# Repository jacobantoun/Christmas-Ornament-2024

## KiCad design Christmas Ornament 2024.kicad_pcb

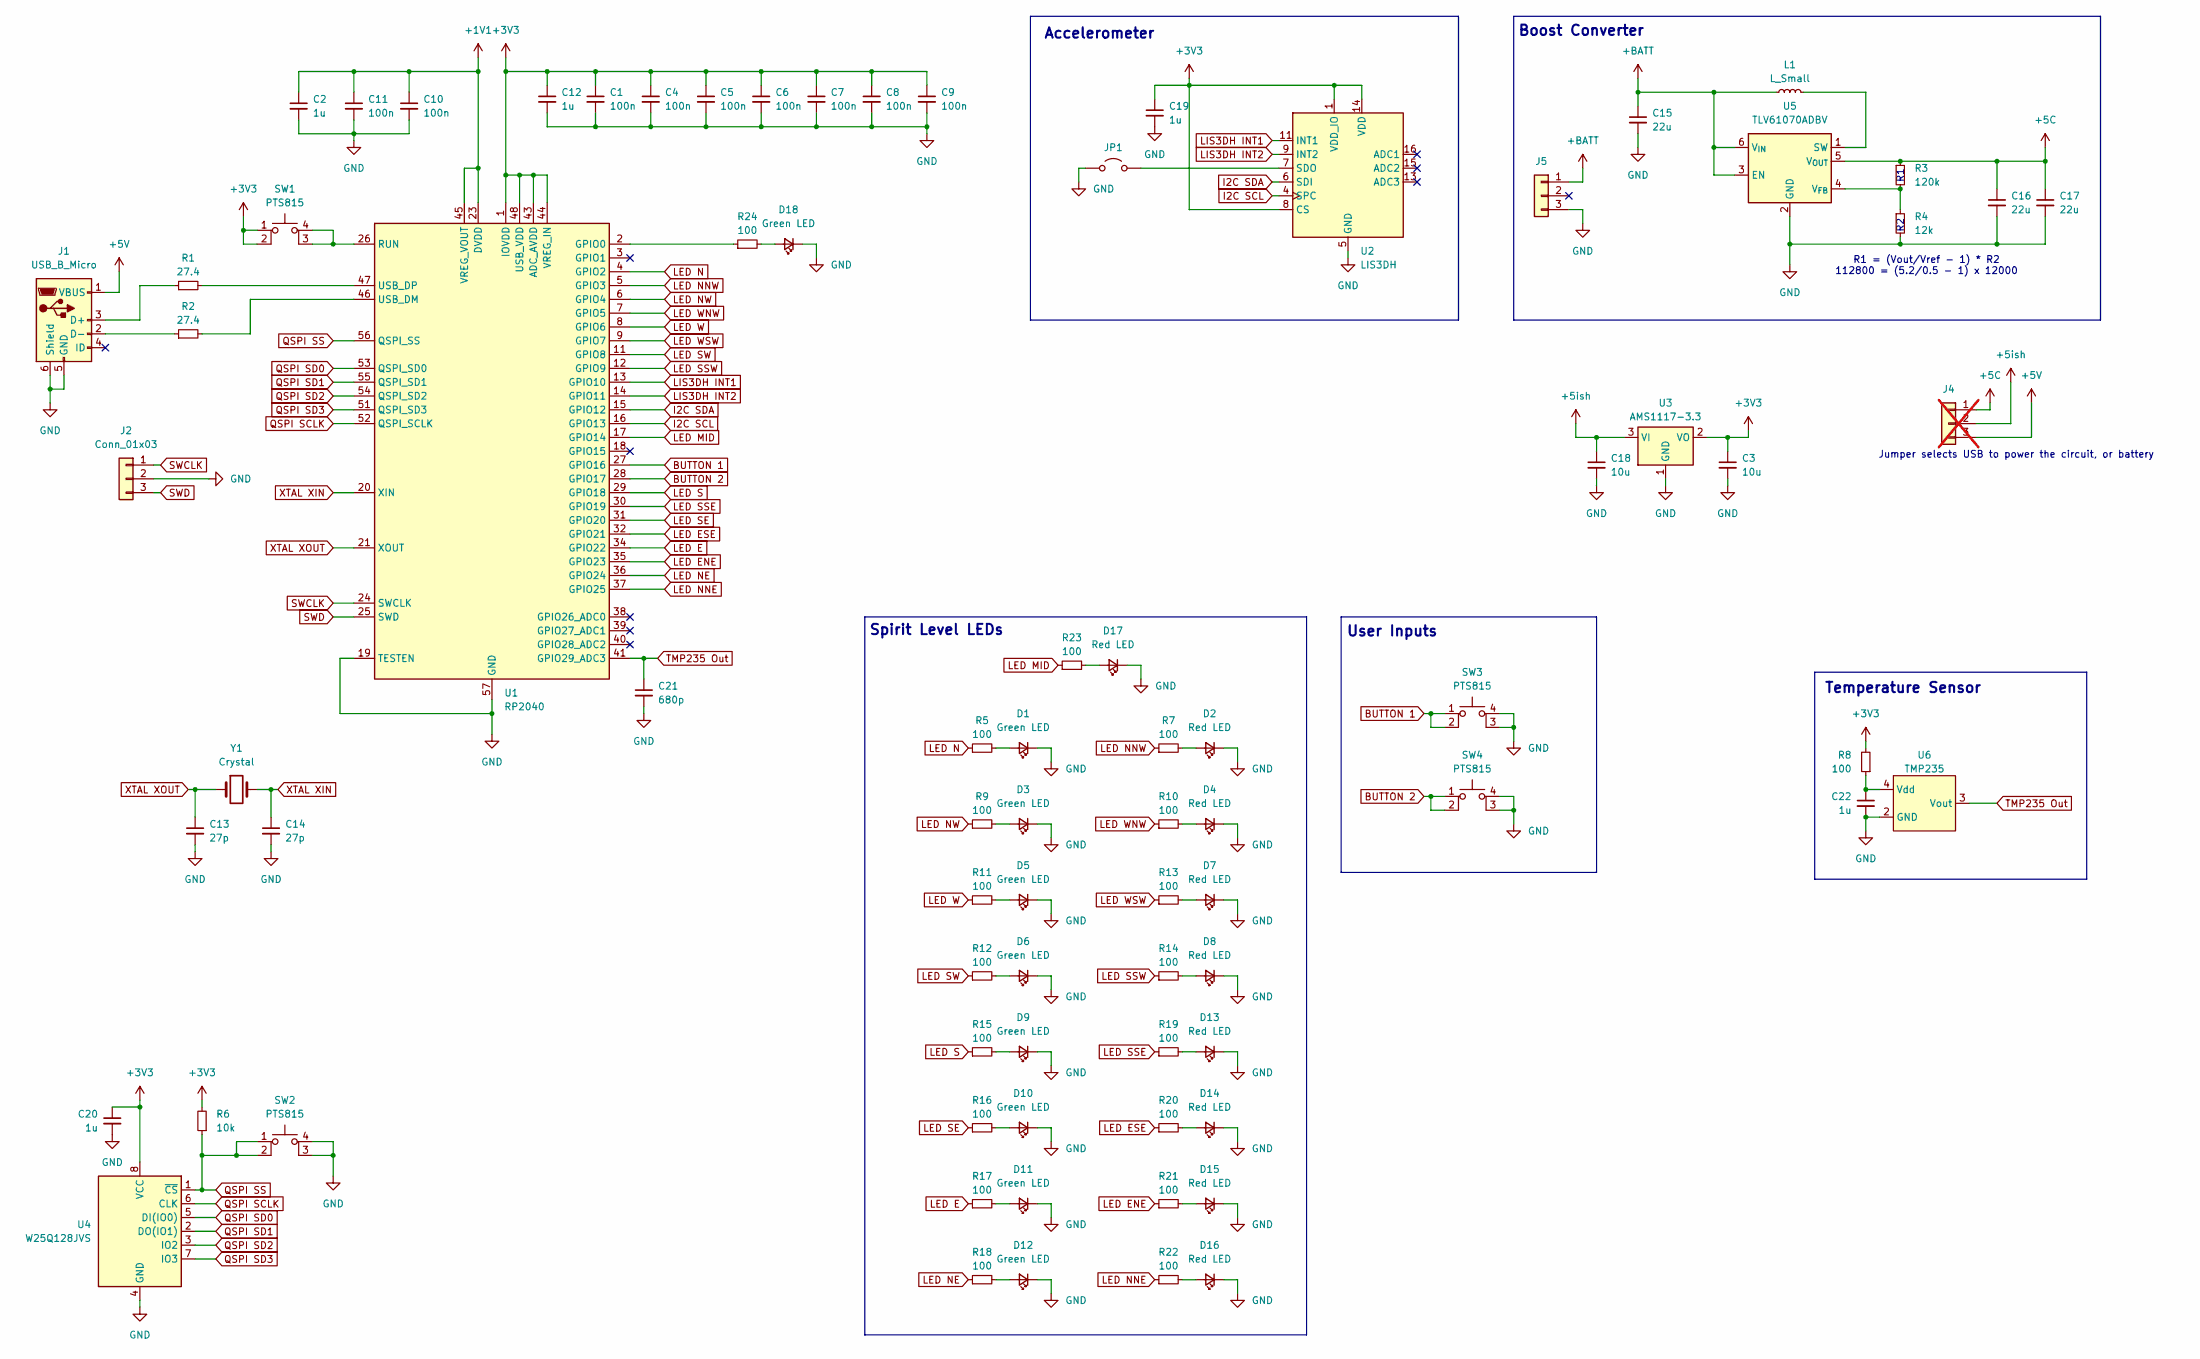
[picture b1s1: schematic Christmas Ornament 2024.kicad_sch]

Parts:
C1, C4, C5, C6, C7, C8, C9, C10, C11: 100n; C_0402_1005Metric_Pad0.74x0.62mm_HandSolder; JLCPCB PN C1525
C2, C12, C19, C20, C22: 1u; C_0402_1005Metric_Pad0.74x0.62mm_HandSolder; JLCPCB PN C52923
C3, C18: 10u; C_0805_2012Metric_Pad1.18x1.45mm_HandSolder; JLCPCB PN C15850
C13, C14: 27p; C_0402_1005Metric_Pad0.74x0.62mm_HandSolder; JLCPCB PN C1557
C15, C16, C17: 22u; C_0805_2012Metric_Pad1.18x1.45mm_HandSolder; JLCPCB PN C45783
C21: 680p; C_0603_1608Metric; JLCPCB PN C1630
D1, D3, D5, D6, D9, D10, D11, D12: Green LED; LED_0805_2012Metric_Pad1.15x1.40mm_HandSolder; JLCPCB PN C2297
D2, D4, D7, D8, D13, D14, D15, D16, D17: Red LED; LED_0805_2012Metric_Pad1.15x1.40mm_HandSolder; JLCPCB PN C2296
D18: Green LED; LED_0805_2012Metric_Pad1.15x1.40mm_HandSolder; JLCPCB PN C2296
J1: USB_B_Micro; USB_Micro-B_Amphenol_10103594-0001LF_Horizontal; JLCPCB PN C428495
J2: Conn_01x03; JST_SH_BM03B-SRSS-TB_1x03-1MP_P1.00mm_Vertical; JLCPCB PN C160389
J4: Conn_01x03; PinHeader_1x03_P2.54mm_Vertical; JLCPCB PN C49257; not fitted
J5: Conn_01x03; PinHeader_1x03_P2.54mm_Vertical; JLCPCB PN DNP
JP1: Jumper_2_Open; SolderJumper-2_P1.3mm_Open_RoundedPad1.0x1.5mm
L1: L_Small; L_Sunlord_SWPA3015S; JLCPCB PN C19734
R1, R2: 27.4; R_0402_1005Metric_Pad0.72x0.64mm_HandSolder; JLCPCB PN C274349
R3: 120k; R_0402_1005Metric; JLCPCB PN C93945
R4: 12k; R_0402_1005Metric; JLCPCB PN C25752
R5, R7, R8, R9, R10, R11, R12, R13, R14, R15, R16, R17, R18, R19, R20, R21, R22, R23, R24: 100; R_0805_2012Metric_Pad1.20x1.40mm_HandSolder; JLCPCB PN C17408
R6: 10k; R_0805_2012Metric_Pad1.20x1.40mm_HandSolder; JLCPCB PN C17414
SW1, SW2, SW3, SW4: PTS815; PTS815 Series; JLCPCB PN C411883
U1: RP2040; QFN-56-1EP_7x7mm_P0.4mm_EP3.2x3.2mm; JLCPCB PN C2040
U2: LIS3DH; LGA-16_3x3mm_P0.5mm_LayoutBorder3x5y; JLCPCB PN C15134
U3: AMS1117-3.3; SOT-223-3_TabPin2; JLCPCB PN C6186
U4: W25Q128JVS; SOIC-8_5.23x5.23mm_P1.27mm; JLCPCB PN C97521
U5: TLV61070ADBV; SOT-23-6; JLCPCB PN C6881375
U6: TMP235; SOT-353_SC-70-5; JLCPCB PN C2861437
Y1: Crystal; Crystal_SMD_Abracon_ABM3-2Pin_5.0x3.2mm; JLCPCB PN C148313

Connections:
+1V1: C2.1, C10.1, C11.1, U1.23 (DVDD), U1.45 (VREG_VOUT), U1.50 (DVDD)
+3V3: C1.1, C3.1, C4.1, C5.1, C6.1, C7.1, C8.1, C9.1, C12.1, C19.1, C20.1, R6.2, R8.2, SW1.1, SW1.2, U1.1 (IOVDD), U1.10 (IOVDD), U1.22 (IOVDD), U1.33 (IOVDD), U1.42 (IOVDD), U1.43 (ADC_AVDD), U1.44 (VREG_IN), U1.48 (USB_VDD), U1.49 (IOVDD), U2.1 (VDD_IO), U2.8 (CS), U2.14 (VDD), U3.2 (VO), U4.8 (VCC)
+5C: C16.1, C17.1, J4.1, R3.1, U5.5 (V_{OUT})
+5V: J1.1 (VBUS), J4.3
+5ish: C18.1, J4.2, U3.3 (VI)
+BATT: C15.1, J5.1, L1.1, U5.3 (EN), U5.6 (V_{IN})
BUTTON 1: SW3.1, SW3.2, U1.27 (GPIO16)
BUTTON 2: SW4.1, SW4.2, U1.28 (GPIO17)
GND: C1.2, C2.2, C3.2, C4.2, C5.2, C6.2, C7.2, C8.2, C9.2, C10.2, C11.2, C12.2, C13.2, C14.2, C15.2, C16.2, C17.2, C18.2, C19.2, C20.2, C21.2, C22.2, D1.1 (K), D2.1 (K), D3.1 (K), D4.1 (K), D5.1 (K), D6.1 (K), D7.1 (K), D8.1 (K), D9.1 (K), D10.1 (K), D11.1 (K), D12.1 (K), D13.1 (K), D14.1 (K), D15.1 (K), D16.1 (K), D17.1 (K), D18.1 (K), J1.5 (GND), J1.6 (Shield), J2.2, J5.3, JP1.1 (A), R4.2, SW2.3 (K), SW2.4 (A), SW3.3 (K), SW3.4 (A), SW4.3 (K), SW4.4 (A), U1.19 (TESTEN), U1.57 (GND), U2.5 (GND), U2.10 (GND), U2.12 (GND), U3.1 (GND), U4.4 (GND), U5.2 (GND), U6.2 (GND)
I2C SCL: U1.16 (GPIO13), U2.4 (SPC)
I2C SDA: U1.15 (GPIO12), U2.6 (SDI)
LED E: R17.1, U1.34 (GPIO22)
LED ENE: R21.1, U1.35 (GPIO23)
LED ESE: R20.1, U1.32 (GPIO21)
LED MID: R23.1, U1.17 (GPIO14)
LED N: R5.1, U1.4 (GPIO2)
LED NE: R18.1, U1.36 (GPIO24)
LED NNE: R22.1, U1.37 (GPIO25)
LED NNW: R7.1, U1.5 (GPIO3)
LED NW: R9.1, U1.6 (GPIO4)
LED S: R15.1, U1.29 (GPIO18)
LED SE: R16.1, U1.31 (GPIO20)
LED SSE: R19.1, U1.30 (GPIO19)
LED SSW: R14.1, U1.12 (GPIO9)
LED SW: R12.1, U1.11 (GPIO8)
LED W: R11.1, U1.8 (GPIO6)
LED WNW: R10.1, U1.7 (GPIO5)
LED WSW: R13.1, U1.9 (GPIO7)
LIS3DH INT1: U1.13 (GPIO10), U2.11 (INT1)
LIS3DH INT2: U1.14 (GPIO11), U2.9 (INT2)
unnamed: D1.2 (A), R5.2
unnamed: D2.2 (A), R7.2
unnamed: D3.2 (A), R9.2
unnamed: D4.2 (A), R10.2
unnamed: D5.2 (A), R11.2
unnamed: D6.2 (A), R12.2
unnamed: D7.2 (A), R13.2
unnamed: D8.2 (A), R14.2
unnamed: D9.2 (A), R15.2
unnamed: D10.2 (A), R16.2
unnamed: D11.2 (A), R17.2
unnamed: D12.2 (A), R18.2
unnamed: D13.2 (A), R19.2
unnamed: D14.2 (A), R20.2
unnamed: D15.2 (A), R21.2
unnamed: D16.2 (A), R22.2
unnamed: D17.2 (A), R23.2
unnamed: D18.2 (A), R24.2
unnamed: J1.3 (D+), R1.1
unnamed: J1.2 (D-), R2.1
unnamed: JP1.2 (B), U2.7 (SDO)
unnamed: SW1.3 (K), SW1.4 (A), U1.26 (RUN)
unnamed: R24.1, U1.2 (GPIO0)
unnamed: R2.2, U1.46 (USB_DM)
unnamed: R1.2, U1.47 (USB_DP)
unnamed: L1.2, U5.1 (SW)
unnamed: R3.2, R4.1, U5.4 (V_{FB})
unnamed: C22.1, R8.1, U6.4 (Vdd)
QSPI SCLK: U1.52 (QSPI_SCLK), U4.6 (CLK)
QSPI SD0: U1.53 (QSPI_SD0), U4.5 (DI(IO0))
QSPI SD1: U1.55 (QSPI_SD1), U4.2 (DO(IO1))
QSPI SD2: U1.54 (QSPI_SD2), U4.3 (IO2)
QSPI SD3: U1.51 (QSPI_SD3), U4.7 (IO3)
QSPI SS: R6.1, SW2.1, SW2.2, U1.56 (QSPI_SS), U4.1 (~CS)
SWCLK: J2.1, U1.24 (SWCLK)
SWD: J2.3, U1.25 (SWD)
TMP235 Out: C21.1, U1.41 (GPIO29_ADC3), U6.3 (Vout)
XTAL XIN: C14.1, U1.20 (XIN), Y1.2
XTAL XOUT: C13.1, U1.21 (XOUT), Y1.1

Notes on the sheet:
Temperature Sensor
Boost Converter
Accelerometer
Spirit Level LEDs
Jumper selects USB to power the circuit, or battery
R1 = (Vout/Vref - 1) * R2 112800 = (5.2/0.5 - 1) x 12000
User Inputs

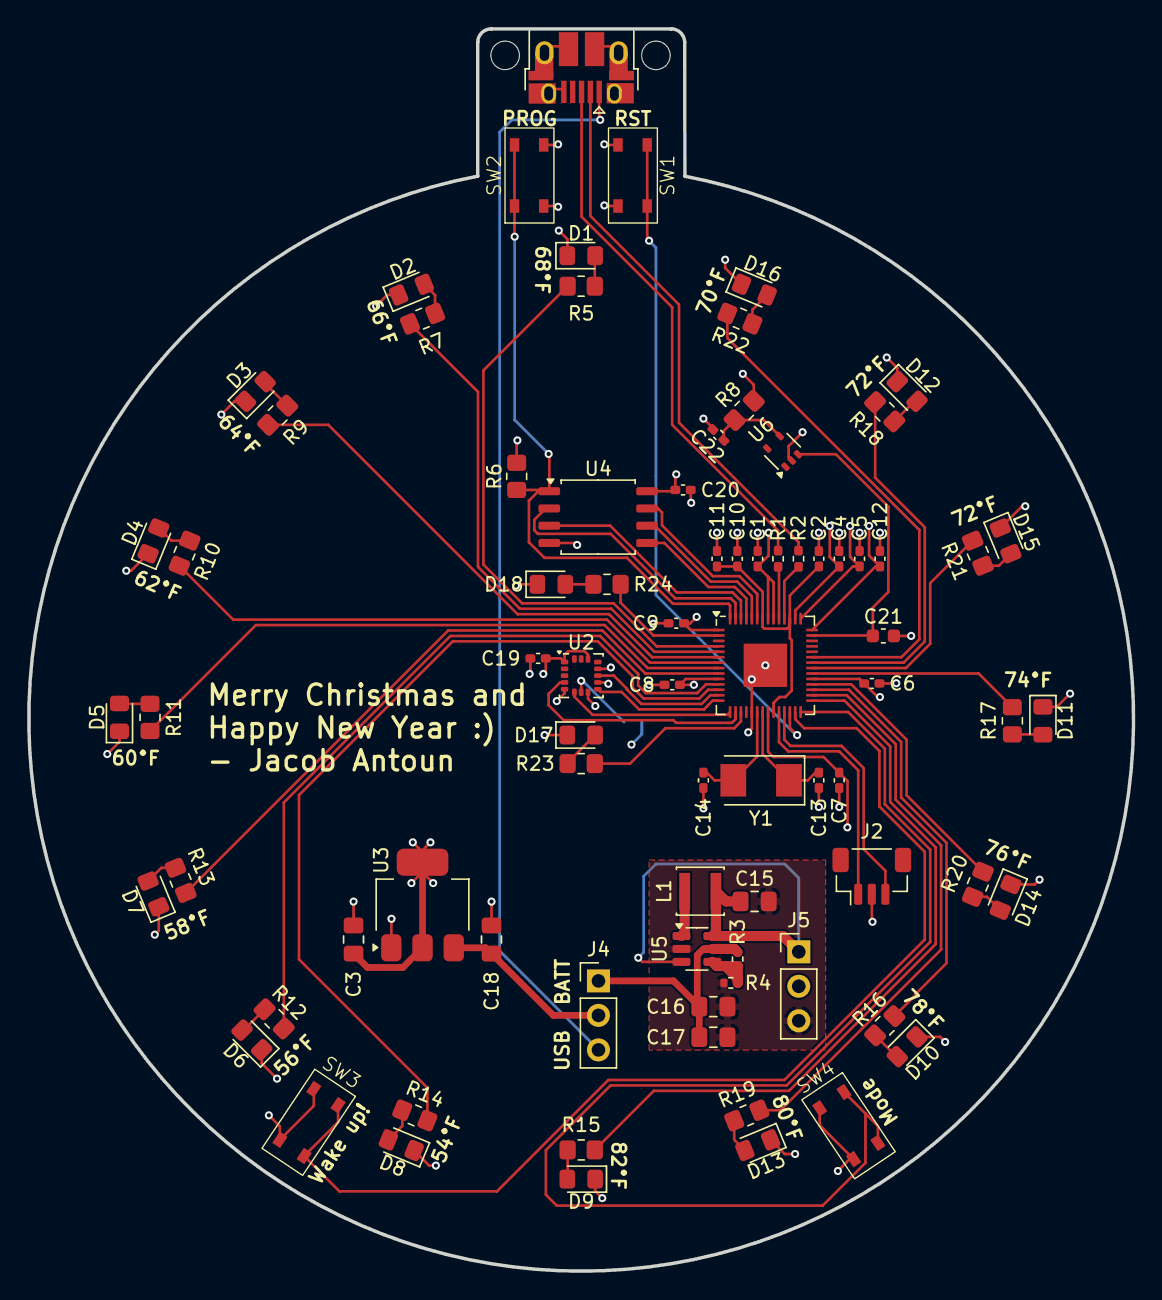
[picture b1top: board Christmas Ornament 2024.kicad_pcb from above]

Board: 4 copper layers, 81.3 x 91.5 mm, 83 parts (1 on the bottom side), 69 nets.

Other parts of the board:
H1, H2: MountingHole; MountingHole_2.1mm

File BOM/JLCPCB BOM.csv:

Comment,Designator,Value,JLCPCB Part #（optional）
16V 100nF X7R Â±10% 0402 Multilayer Ceramic Capacitors,"C1,C4,C5,C6,C7,C8,C9,C10,C11",100n,C1525
25V 1uF X5R Â±10% 0402 Multilayer Ceramic Capacitors,"C2,C12,C19,C20,C22",1u,C52923
"Unpolarized capacitor, small symbol","C3,C18",10u,C15850
50V 27pF C0G Â±5% 0402 Multilayer Ceramic,"C13,C14",27p,C1557
"Unpolarized capacitor, small symbol","C15,C16,C17",22u,C45783
50V 680pF X7R Â±10% 0603 Multilayer Ceramic Capacitors,C21,680p,C1630
-- mixed values --,"D1,D3,D5,D6,D9,D10,D11,D12,D18",Green LED,-- mixed values --
"LED Red, 0805","D2,D4,D7,D8,D13,D14,D15,D16,D17",Red LED,C2296
USB Micro Type B connector,J1,USB_B_Micro,C428495
"Generic connector, single row, 01x03, script generated (kicad-library-utils/schlib/autogen/connector/)",J2,Conn_01x03,C160389
"Generic connector, single row, 01x03, script generated (kicad-library-utils/schlib/autogen/connector/)",J5,Conn_01x03,DNP
"Inductor, small symbol",L1,L_Small,C19734
27.4Î© 0402 Chip Resistor,"R1,R2",27.4,C274349
"Resistor, small symbol",R3,120k,C93945
"Resistor, small symbol",R4,12k,C25752
"Resistor, small symbol","R5,R7,R8,R9,R10,R11,R12,R13,R14,R15,R16,R17,R18,R19,R20,R21,R22,R23,R24",100,C17408
"Resistor, small symbol",R6,10k,C17414
PTS815,"SW1,SW2,SW3,SW4",PTS815,C411883
A microcontroller by Raspberry Pi,U1,RP2040,C2040
"3-Axis Accelerometer, 2/4/8/16g range, I2C/SPI interface, LGA-16",U2,LIS3DH,C15134
"1A Low Dropout regulator, positive, 3.3V fixed output, SOT-223",U3,AMS1117-3.3,C6186
"128Mb Serial Flash Memory, Standard/Dual/Quad SPI, SOIC-8",U4,W25Q128JVS,C97521
"Boost Converter, 2.5A switch current limit, 2.2-5.5V Output Voltage, 0.5-5.5V Input Voltage, SOT-23-6",U5,TLV61070ADBV,C6881375
SENSOR ANALOG -40C-150C SC70-5,U6,TMP235,C2861437
Two pin crystal,Y1,Crystal,C148313

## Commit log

2024-11-22 Add LEDs and resistors
2024-11-22 Schematic Finished
2024-11-22 Ready for Layout
2024-11-23 PCB Layout beginning
2024-11-23 Changed feedback resistor sizes
2024-11-24 Layout in progress...
2024-11-25 PCB Layout and Routing complete
    DRC
2024-11-26 Silkscreen in progress
2024-11-26 BOM and Gerber export
2024-11-26 deleted gerbers not in folder
2024-11-26 BOM and CPL ready for ordering
2024-11-26 saved
2024-12-11 Added firmware
2024-12-11 Added TMP235 variables
2024-12-12 Added temp F
    Temperature seems to be off by a few degrees...
2024-12-15 Added spirit level and temperature functionality
2024-12-15 kicad save
2024-12-17 Added mode switching
    Need to add PWM to temperature LEDs
2024-12-19 how tf do i sleep
2024-12-19 Added pico_extras
2024-12-20 This program sucks ass
2024-12-20 Create pico extras
